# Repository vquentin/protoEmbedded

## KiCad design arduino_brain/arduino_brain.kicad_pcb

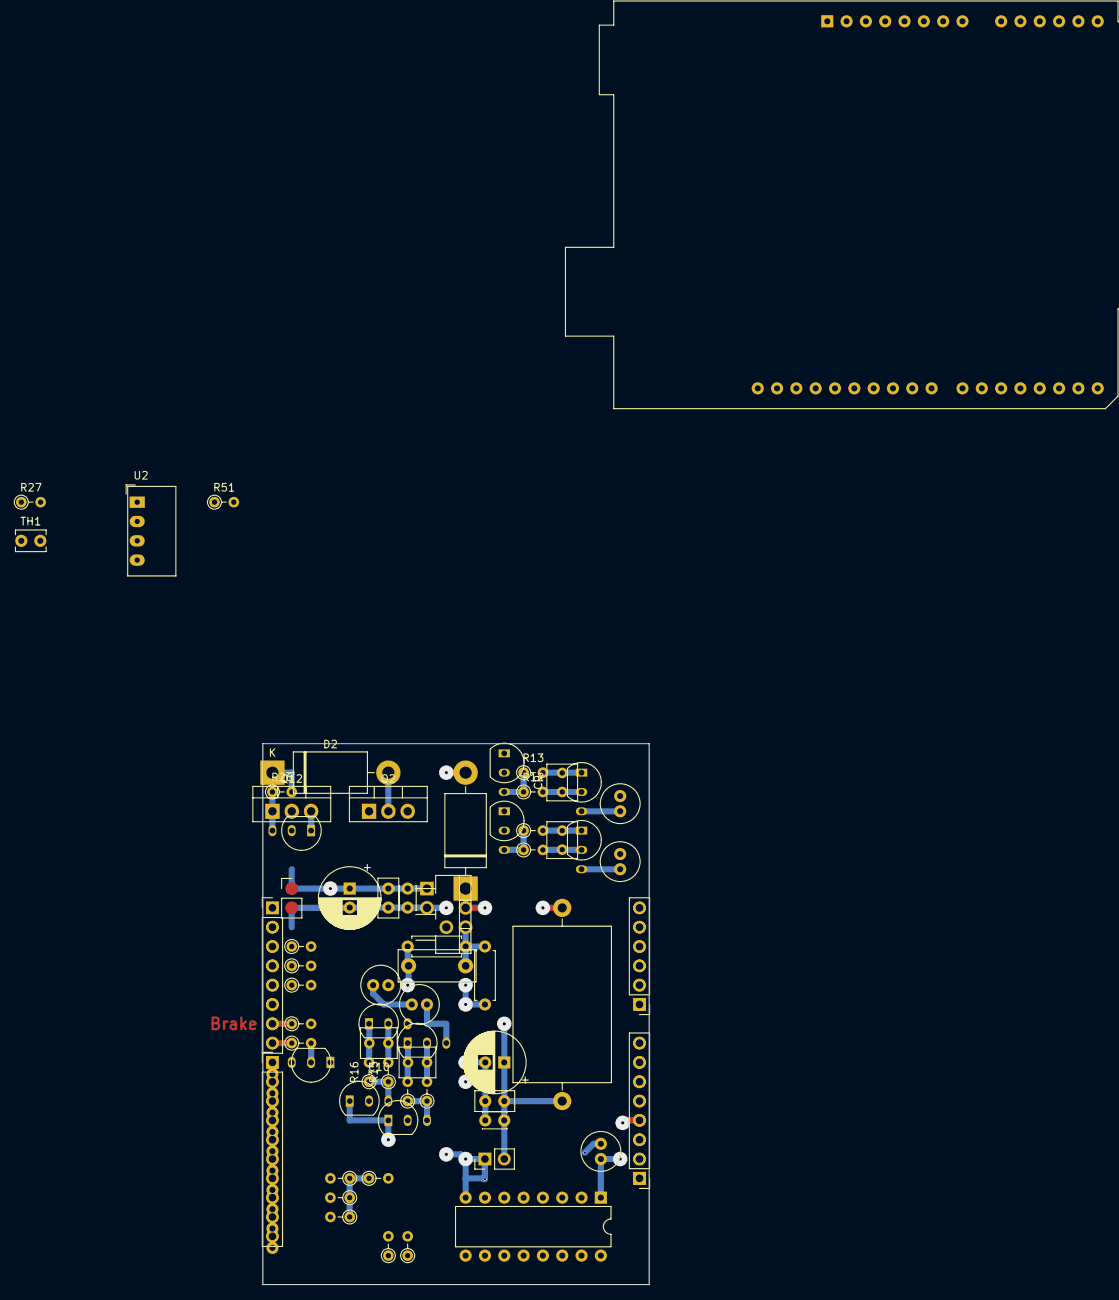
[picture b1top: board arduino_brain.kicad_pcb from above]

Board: 4 copper layers, 50.8 x 71.1 mm, 67 parts (0 on the bottom side), 56 nets.

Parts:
A1, A2: Arduino_UNO_R3
C1: EEU-FC1E471L; CP_Radial_D8.0mm_P2.50mm
C2, C6: FG16X5R1E476MRT06; C_Disc_D5.0mm_W2.5mm_P2.50mm
C3, C8: C320C104M5R5TA; C_Disc_D3.0mm_W2.0mm_P2.50mm
C5: PHE450MK4470JR05; C_Rect_L10.0mm_W4.0mm_P7.50mm_FKS3_FKP3
C7: RL81C101MDN1KX; CP_Radial_D8.0mm_P2.50mm
C9, C10, C11, C12: RDEC71E476MWK1H03B; C_Rect_L4.6mm_W3.8mm_P2.50mm_MKS02_FKP02
C13, C14, C15, C16: ECA-1EHG470; C_Radial_D5.0mm_H11.0mm_P2.00mm
C17: 220uF; C_Radial_D5.0mm_H11.0mm_P2.00mm
D1, D2: SB560; D_DO-201AD_P15.24mm_Horizontal
J1, J3: Conn_01x08_Male; PinHeader_1x08_P2.54mm_Vertical
J2: Conn_01x10_Male; PinHeader_1x10_P2.54mm_Vertical
J4: Conn_01x06_Male; PinHeader_1x06_P2.54mm_Vertical
J5: 12V cable from regulator; PinHeader_1x02_P2.54mm_Vertical
J6: 7.5V cables x2 to Arduino power jacks; PinHeader_1x02_P2.54mm_Vertical
L1: AIAP-03-470K; L_Axial_L20.3mm_D12.7mm_P25.40mm_Horizontal_Vishay_IHA-201
Q1, Q3, Q4, Q6, Q8, Q10: 2N3904; TO-92_Inline
Q2: TIP120; TO-220-3_Vertical
Q5, Q7, Q9, Q11: 2N3906; TO-92_Inline
Q12: STP36NF06L; TO-220-3_Vertical
R4, R6, R7, R8, R25, R26, R51: CFR16-10k; R_Axial_DIN0204_L3.6mm_D1.6mm_P2.54mm_Vertical
R9: CFR16-100R; R_Axial_DIN0204_L3.6mm_D1.6mm_P2.54mm_Vertical
R10: CFR16-1k; R_Axial_DIN0204_L3.6mm_D1.6mm_P2.54mm_Vertical
R11: CFR16-3k3; R_Axial_DIN0204_L3.6mm_D1.6mm_P2.54mm_Vertical
R12: CFR16-1k0; R_Axial_DIN0204_L3.6mm_D1.6mm_P2.54mm_Vertical
R13: CFR16-1k2; R_Axial_DIN0204_L3.6mm_D1.6mm_P2.54mm_Vertical
R14, R16: CFR16-4k7; R_Axial_DIN0204_L3.6mm_D1.6mm_P2.54mm_Vertical
R15: CFR16-1k8; R_Axial_DIN0204_L3.6mm_D1.6mm_P2.54mm_Vertical
R17, R20: CFR16-8k2; R_Axial_DIN0204_L3.6mm_D1.6mm_P2.54mm_Vertical
R18, R21, R27: CFR16-2k7; R_Axial_DIN0204_L3.6mm_D1.6mm_P2.54mm_Vertical
R19, R22: CFR16-22k; R_Axial_DIN0204_L3.6mm_D1.6mm_P2.54mm_Vertical
R23: CFR-25JB-1K0; R_Axial_DIN0207_L6.3mm_D2.5mm_P7.62mm_Horizontal
R24: CFR-25JB-52-4K7, 4.64 k ideally; R_Axial_DIN0207_L6.3mm_D2.5mm_P7.62mm_Horizontal
TH1: Thermistor; C_Disc_D3.8mm_W2.6mm_P2.50mm
U1: LM2596T-ADJ; TO-220-5_P3.4x3.7mm_StaggerOdd_Lead3.8mm_Vertical
U2: CRE1S2412SC; Converter_DCDC_muRata_CRE1xxxxxxSC_THT
U3: CD4050BE; DIP-16_W7.62mm

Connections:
+3V3: A1.4, C17.1, J3.4, U3.1
+5V: A1.5, J3.5, R4.1, R6.1, R7.1, R25.1, TH1.1
+7.5V: A1.8, A2.8, C5.2, C6.1, C7.1, C8.1, J3.8, J6.2, L1.2, R24.2
A1_A0: A1.9, J4.1, R27.1, TH1.2
A1_A1: A1.10, J4.2
A1_A2: A1.11, J4.3, R4.2, R51.1
A1_A3: A1.12, J4.4
A1_A4: A1.13, A2.13, J4.5
A1_A5: A1.14, A2.14, J4.6
A1_D0: A1.15, J1.1, R20.1
A1_D1: A1.16, J1.2, R17.1
A1_D2: A1.17, J1.3, R6.2
A1_D3: A1.18, J1.4, R9.1
A1_D4: A1.19, J1.5, R25.2
A1_D5: A1.20, J1.6, R7.2
A1_D6: A1.21, J1.7, R11.1
A1_D7: A1.22, J1.8, R8.1
A1_D8: A1.23, J2.1, U3.9
A1_D9: A1.24, J2.2, U3.14
A1_D10: A1.25, J2.3, U3.7
A1_D11: A1.26, J2.4, U3.5
A1_D12: A1.27, J2.5
A1_D13: A1.28, J2.6, U3.3
A2_D5: A2.20, R10.1
A2_D6: A2.21, R14.1
ARDUINO_ICSP_4: A2.1, A2.28
BEAM_+12V: C1.1, C2.1, C3.1, C9.2, C10.2, C11.2, C12.2, D2.1, J5.1, Q5.1, Q7.1, Q9.1, Q11.1, R13.2, R16.2, R19.2, R22.2, R26.2, U1.1, U2.4
COMMODO_GND: A1.1, A1.6, A1.7, A1.29, A2.7, C1.2, C2.2, C3.2, C6.2, C7.2, C8.2, C13.2, C14.2, C15.2, C16.2, C17.2, D1.2, J2.7, J3.6, J3.7, J5.2, J6.1, Q2.3, Q3.1, Q4.1, Q6.1, Q8.1, Q10.1, Q12.3, R23.1, R27.2, U1.3, U2.1, U2.3, U3.8
HORN_GND: D2.2, Q2.2
INDICATOR_L_+12V: C16.1, Q11.3
INDICATOR_R_+12V: C15.1, Q9.3
unnamed: A1.2, J3.2
unnamed: A1.3, J3.3
unnamed: A1.30, J2.8
unnamed: A1.31, J2.9
unnamed: A1.32, J2.10
unnamed: C5.1, R23.2, R24.1, U1.4
unnamed: C9.1, Q5.2, R12.2
unnamed: C10.1, Q7.2, R15.2
unnamed: C11.1, Q9.2, R18.2
unnamed: C12.1, Q11.2, R21.2
unnamed: D1.1, L1.1, U1.2
unnamed: Q1.2, R8.2
unnamed: Q2.1, R9.2
unnamed: Q3.2, R10.2
unnamed: Q4.2, R11.2
unnamed: Q4.3, R12.1, R13.1
unnamed: Q6.2, R14.2
unnamed: Q6.3, R15.1, R16.1
unnamed: Q8.2, R17.2
unnamed: Q8.3, R18.1, R19.1
unnamed: Q10.2, R20.2
unnamed: Q10.3, R21.1, R22.1
unnamed: Q3.3, Q12.1, R26.1
TAILLIGHT_BRAKE: C13.1, Q5.3
TAILLIGHT_TAILLIGHT: C14.1, Q7.3

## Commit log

2020-01-03 Added 5V regulator to schematic
2020-01-03 Added diode to 5V regulator
2020-01-03 Added 12V switching regulator, eco mode control and cleaned schematic
2020-01-03 Cleaned up the notations
2020-01-03 Designed horn state machine
2020-01-03 Simplified horn state machine design
2020-01-03 Simplified turn signal state machine
2020-01-06 Cleaned up horn state machine design
2020-01-06 Implemented horn state machine
2020-01-06 Added debounce library and implemented switch debouncing
2020-02-03 Better transistors, 5 to 7V for Arduino rail and duplicate brake and speed outputs.
2020-02-03 Implemented components for 12 to 7 V buck
2020-02-04 Switching regulator with components as selected from EE tutorial - not working
2020-02-05 12 to 7 V stage on protoboard - 7V output confirmed!
2020-02-06 Included thermal characteristics of 12 to 7 V stage
2020-02-06 Implemented horn circuit on breadboard. Working, but multimeter cannot read voltage drop.
2020-02-06 Added horn tune commands, but not in state machine with separate button
2020-02-06 Cleaned up Arduino board connections
2020-02-07 Cleaned up connections
2020-02-07 Adapted brake light R values
2020-02-07 Added horn cap
2020-02-07 Removed horn cap
2020-02-10 Added light state machine, for testing
2020-02-10 Added bypass capacitor near PNP switch
2020-02-10 Modified bypass capacitor near PNP switch
2020-02-10 Introduced snubber circuit in parralel to horn and removed bypass capacitor
2020-02-10 Beefed up snubber capacitor
2020-02-10 Swapped cap and res snubber
2020-02-10 Added cap on supply, removed snubber cap
2020-02-11 Removed cap on supply
2020-02-11 Added capactitor between base and emitter of pnp transistor horn
2020-02-11 Added capactitor in parallel to R2 (EE.SE), removed the previous cap
2020-02-11 Added capactitor between Q3B and Q3E (EE.SE), removed the previous cap
2020-02-11 Caps between Q4 and Q3 B-C, SB560 replacing SB330
2020-02-11 Still not working
2020-02-12 Added LTSpice simulations
2020-02-12 Added soft horn in state machine schematic
2020-02-12 Removed resistor in series with diode (results not conclusive)
2020-02-12 Included soft horn and alarm cases for horn state machine
2020-02-12 Attached speed sensor to interruptable pin
2020-02-13 Horn state machine debugged and working
2020-02-13 Almost solved LED flickering with horn on issue
2020-02-13 Started implementing OLED screen
2020-02-14 Finished implementing OLED screen
2020-02-17 Added battery indicator to display testing routines
2020-02-17 Variabilized the battery outline
2020-02-17 Included speed display
2020-02-17 Included distances trip, odo, battery remaining
2020-02-17 Implemented brake state machine
2020-02-17 Implemented eco mode state machine
2020-02-17 Described turn signal FSM - not implemented
2020-02-18 implemented turn signal state machine and i2c communication with master of receive messages
2020-02-18 implemented i2c communication with master of receive messages and unsigned long conversion
2020-02-18 added OLED routines
2020-02-18 added OLED routines with new files
2020-02-18 Moved strings to flash with F() macro
2020-02-20 Laid out the protoboard components
2020-02-20 Implemented turn signal detection with analog states
2020-02-20 Updated PCB
2020-02-20 Started routes on PCzb, locking components already placed
2020-02-20 Finsihed solder routes on PCB
2020-02-23 almost finished the layout of passives
